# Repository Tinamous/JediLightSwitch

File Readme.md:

Jedi LightSwitch
================

The Jedi Light Switch is a home automation light switch which responds to the Jedi wave or touch(1). It aims to bring the humble wall switch into the modern WiFi lighting era.

1) Automation of modern WiFi lamps (LIFX/Hue) doesn't work if the lamp is switch off at the wall switch.
2) Existing switch may not work as expected for visitors with WiFi bulbs. Often the switch is on but the light off.
3) Switching the lights on/off via an app is annoying.
4) The wall switch may be difficult or impossible to replace with a automation friendly version. (Excludes the Jedi Lightswitch :-) )
5) The existing switch is single use, it switches on or off the main light. In a modern house their are many things this switch can be doing.

The Jedi Light Switch is PCB based with a custom 3D printed enclosure. It is powered by a Particle Photon which uses WiFi and optionally cloud services (i.e. IFTTT.com / Tinamous.com) to control and monitor the room environment.

The Photon may be user programmed so the switch may be heavily customised as desired, even OTA after installation. Likewise lighting control via IFTTT may be modified at will.

As well as acting as a switch it also acts as a room sensor with built-in temperature, humidity and light level measurements which may be used for further automation tasks.

Proximity detection allowing the sensing if somebody is close to the switch. (e.g. Switch the lights on in the room if they are not and somebody is close to the switch as they are probably about to try and switch them on anyway).

Two LEDs controlled by the Photon give the immediate feedback (cloud sevices may take a few seconds to perform the apporpiate operations), these LEDs may also be internet controlled to draw attention to something (i.e. the doorbell ringing).

Why:
----
If you have LIFX or Hue lights they stop working once somebody switches them off at the wall switch which can ruin your automation plans. The Hue has a small switch however the LIFX lights rely on 3rd party products for switching, both suffer from our built-in tendandy to switch the light off at the switch as we leave the room. Neither lights work so well when that happens! Neither Hue or LIFX switch options are immediatly obious that they should be used in preference to the wall switch. Nobody wants to have to train their guests how to switch the lights on or off.

Imaging the scene. You walk into your room, the lights are off but the light switch is on.
* Option 1: Switch the light switch off then on again. This works a charm (but only for the main light).
* Option 2: 
** Find your phone (hopefully it's not somewhere in the dark room you are walking into)
** Unlock your phone
** Launch the LIFX application
** Wait whilst the LIFX applicaiton loads
** Try not to trip or walk into anything as you've continued to walk whilst working your phone in the darkened room
** Scroll to the bulbs or scene you wish to set
** Select the bulbs or scene
** Hopefully the lights respond first time, if not wait a bit and try again
** Put phone away
** Think how great it is you can control your lights from your phone...

Leaving a room:
---------------
Nobody likes to leave the lights on in rooms that are unused or when you go out.....

Imaging you leave the room.
* Option 1: Flick the light switch to switch the light off (goodbye automation).
* Option 2: Find your phone, unlock your phone (you see where this is going).

Neither of these senarios are great. You could replace or remove the light switch...

The Light Switch Problem:
-------------------------
* In the UK we have a different style and voltage requirement for light switchs compared to USA, hence home automation products are slow (if ever) to reach the UK market.
** This is not helped by the need for a CE mark which is slow and expensive.
** Often the switches that are available are extreamly cheap (I've had 5x £30 switches fail when the incandecent bulb blew).
* Most HA light switches require a minimum of 25mm backing box. A lot of UK homes use a 15mm box which either means you need to pad the switch out on the wall (ugly) or replace the box (painful).
* A lot (almost all) HA light switches require "3 wire" configuration. Live, Neutral and switch return. Most UK homes have only 2 wire switches (Live and return).
* Not everybody wants to play with the electrics to get a fancy light switch fitted or pay for an expensive electrician.
** If it's a 2 wire replacement this isn't too difficult, changing the 2 wires to 3 and/or replacing the backing box are a big job.
* If you rent chances are you are not allowed to replace the light switch anyway. Who wants to get thrown out of their rented accomodation for a bit of home automation goodness!
* Switching the lights off at the light switch ruins automation.
* The light switch generally only controlls the main light, occasionally wall lights.
* Switching the wall switch on or off doesn't tell your home automation system that the action has happened so no further actions can happen based on that.
* Theirs no intelligence in the on/off of the humble wall switch. If you walk into a room when you're still half asleep having the light come on at 100% brightness is painful.

The Solution:
-------------
The Jedi Light Switch is designed to remove those problems through a two part solution. The main part is the touch and gesture sensitive WiFi based switch PCB, the second is the enclosure.

The switch and enclosure are designed to be simple to install, no re-wiring required (except for external USB power), a direct replacement for the humble wall switch whilst leaving the switch in place, just hidden behind some sexy technology.

The current enclosure is designed to fit over a UK light switch (sorry rest of the world, It may work in Europe, it certainly won't fit over USA switches). 

The enclosure is 3D printed in two parts:

1) The base. This has an overlap area that fits between the wall and the existing switch to secure the base in place and only requires the switch to be loosened and not removed.
** To fit loosen the screws on the light switch slightly so that the switch comes forward about 2mm.
** Slide the base down the wall so the back fits between the wall and the switch until the top of the switch is as close to the top of the base as it can go.
** Tighten the switch screws, ensuring the enclosure is level. This clamps the base part to the wall. No other fixing is required.
2) The cover:
** This is optional. You may if you wish attach the switch PCB via glue or screws to the base and be done.
** The cover gives a nicer finish to the switch whilst also providing mechanical fixing of the PCB within the base. It may be printed in any colour you can get the 3D filament or resin for, although clear works well.
** Optional: You may also print on a clear "acetate film" to fit between the cover and the PCB with a nice pattern or design over the touch sensor.
** The cover simply slides over the base with the PCB in the middle and stays in place by friction making it easy to remove should you need access to the actual wall switch.

Other Advantages:
* Use of gesture to switch the lights on would work well in dirty/wet areas (e.g. the kitchen) where you may not wish to touch something (e.g. you've half way through cooking chicken).
* The switch supports up, down, near and far waves as well, these may be used to dim the lights, control additional (hall/landing) lighting or something else.
* You don't actually need an existing light switch. The case could be directly attached to the wall or something else to provide easy additional lighting points.
* Other than a USB power pack and WiFi no other external parts are required (no Hub, no dedicated lighting wiring, no ......, not even screws or double sided sticky tape)
* You don't have to be British (but it helps). The switch enclosure and PCB are sized to cover a UK light switch, however as they can be used in stand-alone mode they don't have to be used with a UK switch.
** The SCAD design for the enclosure is provided which may be modified to fit other requirements.
* Intellegent:
** The lights could be dimmed to brightness greadually, especially if the switch knew the room was very dark previously.
** or set to automatically switch off or dim the lifhts after 2 hours.
** or the air-con switched on if the room is hot and humid and the lights have just been switched on (or off).
** the curtains could be closed automatically when the lights are switched on.
** the whole house lights could be switched off if the hall light was switched off (and vica versa, house lights switched on when it's dark when hall/door switch is switched on).

Limitation:
-----------

* Currently requires external USB 5V DC power as the Photon is relativly fairly power hungry device (i.e. using WiFi). Even if a battery was fitted it would require a fair size and to be topped up regularly particularly if the switch is required to respond to network actions (e.g. light LEDs, update firmware etc.).

* Lack of a traditional switch mechanism which may confuse guests. Hopefully the touch ability would be enough to make up for this.

* Cloud services can be slow. Using Photon -> Particle.io -> IFTTT -> LIFX.com -> LIFX bulb can be seconds in the trip which is not idea for a light switch. In this time a new user may have told the switch to switch on/off/on/off/on etc a number of times.

Future upgrades:
----------------

Planned for V1.1:
* 2 LEDs in the bottom corners to match the top so each corner has an LED.
* Back lighting. Adding more LEDs to project backwards to light up the enclosure (works best for clear enclosures). Ideally NeoPixel type so they can be controlled from 1 wire and have a range of colour / intensity controlled.

Future posabilities:
* Split/Dual touch sensor pads so that it works for hall/landing lights (up/down) or duel lighting modes in a room (main/wall lights).
* RS485 interface, supply 5V to Photon from a RS485 with 12V house wired RS485 network, interface with other RS485 HA devices and provide a more reliable connection and power.
** This is easier then putting a PoE Ethernet connection on the switch.
* Battery + charger
* Improved interrupt's that can be used to wake the Photon (currently 2 interupts, one high and one low which can't both be used to wake the Photon) to improve battery life.
* Buzzer
* IR Sender to allow the switch to send out instructions from automation requests (e.g. telly on) or relay the signal from room to room.
* IR Receiver to allow remove control of the switch and/or transmission from room to room.
* Microphone (to decect noise levels rather than listen).
* PIR sensor
* Improved temp/humidity sensor for one of the new Bosch line with BP and gas sensing as well.

License:
--------
Licensed under Creative Commons ShareAlike 4.0 https://creativecommons.org/licenses/by-sa/4.0/

Restrictions: May not be used to control lighting on a death star.

Notes:
------
1) Also responds to non-Jedi waves and touch. Not to be used where control by non-Jedi personel is restricted.

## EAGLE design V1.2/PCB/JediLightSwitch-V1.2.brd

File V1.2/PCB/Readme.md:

Jedi LightSwitch PCB.
=====================

Licensed under Creative Commons ShareAlike 4.0 https://creativecommons.org/licenses/by-sa/4.0/

PCB Fabrication by OSH Park.
PCB: <TODO: Insert PCB link>

PCB Stensil by OSH Stencil (https://oshstencils.com/).

PCB Assembly Notes:
-------------------
APDS-9960 and HTU21D are tricky components to solder onto the board. The switch may be used without them if you wish to not solder them and prefer to use touch only.

Use either a hot air gun for solder reflow or reflow oven for the top layer. Use a stencil from OSH Stencils and place U1/U2 (APDS-9960 and HTU21D) carefully. 

Using a low flow and a temperature appropriate for the solder paste heat the board around U1/U2 bringing until the solder melds. Allow a little longer for U1 as the solder is not visible.

The bottom of the board should be hand solderered to prevent U1/U2 dropping off. Most parts are 1206 or 0805 and not overly difficult. U4 (AT42QT1010) is a little difficult but excess solder can be removed with solder wick if needed.

The value of C4 may need to be adjusted to increase/reduce sensitivity. 10nF was found to be to little. 68nF was overly sensitive.

The value of R5/R6 should be selected based on the required brightness of the LEDs and the LED selected.

Resources:
----------
SparkFun Eagle Library and breakout boards used under CC-SA.

SparkFun Eagle Library: https://github.com/sparkfun/SparkFun-Eagle-Libraries

SparkFun APDS-9960 breakout: https://www.sparkfun.com/products/12787
SparkFun HTU21D breakout: https://www.sparkfun.com/products/12064
SparkFun AT42QT1010 breakout: https://www.sparkfun.com/products/12041

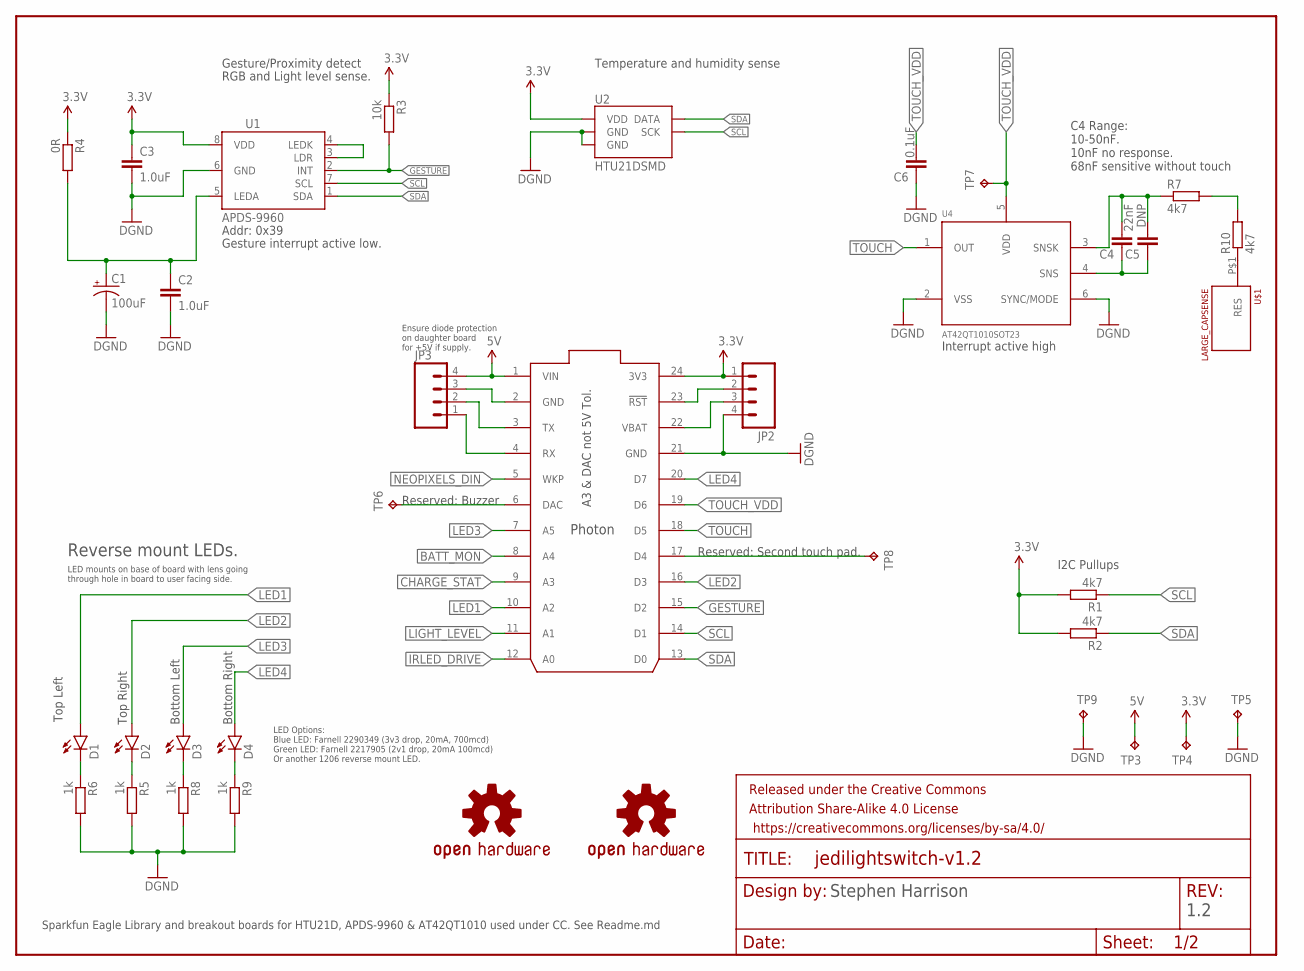
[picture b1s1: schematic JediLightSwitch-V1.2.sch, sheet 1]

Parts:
C1: 100uF; EIA7343
C2, C3: 1.0uF; C0805
C4: 22nF; C0805
C5: DNP; C0805
C6: 0.1uF; C0805
D1, D2, D3, D4: LED1206-BOTTOM; LED-1206-BOTTOM
FRAME2: FRAME-LETTER; CREATIVE_COMMONS
JP2, JP3: M04SMD_STRAIGHT_COMBO; 1X04_SMD_STRAIGHT_COMBO
LOGO1, LOGO2: OSHW-LOGOM; OSHW-LOGO-M
R1, R2, R7, R10: 4k7; R0805
R3: 10k; R0805
R4: 0R; R0805
R5, R6, R8, R9: 1k; R0805
TP3, TP5, TP6, TP7, TP8, TP9: TPTP20R; TP20R
TP4: 3v3; TP20R
U1: APDS-9960
U2: HTU21DSMD; HTU21D
U3: PHOTON_SMD
U4: AT42QT1010SOT23; SOT23-6
U$1: LARGE_CAPSENSE

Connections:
3.3V: C3.1, JP2.1, R1.2, R2.2, R3.1, R4.1, TP4.TP, U1.8 (VDD), U2.VDD, U3.24 (3V3); also elsewhere on the board
5V: JP3.4, TP3.TP, U3.1 (VIN); also elsewhere on the board
BATT_MON: U3.8 (A4); also elsewhere on the board
CHARGE_STAT: U3.9 (A3); also elsewhere on the board
D4: TP8.TP, U3.17 (D4)
DAC: TP6.TP, U3.6 (DAC)
GESTURE: R3.2, U1.2 (INT), U3.15 (D2)
GND: C1.C (-), C2.2, C3.2, C6.1, JP2.4, JP3.3, R5.2, R6.2, R8.2, R9.2, TP5.TP, TP9.TP, U1.6 (GND), U2.7 (GND), U2.GND, U3.2 (GND), U3.21 (GND), U4.2 (VSS), U4.6 (SYNC/MODE); also elsewhere on the board
IRLED_DRIVE: U3.12 (A0); also elsewhere on the board
LED1: D1.A, U3.10 (A2)
LED2: D2.A, U3.16 (D3)
LED3: D3.A, U3.7 (A5)
LED4: D4.A, U3.20 (D7)
LIGHT_LEVEL: U3.11 (A1); also elsewhere on the board
unnamed: U1.3 (LDR), U1.4 (LEDK)
unnamed: C1.A (+), C2.1, R4.2, U1.5 (LEDA)
unnamed: D2.C, R5.1
unnamed: D1.C, R6.1
unnamed: JP2.2, U3.23 (!RST)
unnamed: JP2.3, U3.22 (VBAT)
unnamed: R7.2, R10.2
unnamed: R10.1, U$1.P$1
unnamed: JP3.1, U3.4 (RX)
unnamed: JP3.2, U3.3 (TX)
unnamed: C4.2, C5.2, R7.1, U4.3 (SNSK)
unnamed: C4.1, C5.1, U4.4 (SNS)
unnamed: D3.C, R8.1
unnamed: D4.C, R9.1
NEOPIXELS_DIN: U3.5 (WKP); also elsewhere on the board
SCL: R1.1, U1.7 (SCL), U2.SCK, U3.14 (D1); also elsewhere on the board
SDA: R2.1, U1.1 (SDA), U2.DATA, U3.13 (D0); also elsewhere on the board
TOUCH: U3.18 (D5), U4.1 (OUT)
TOUCH_VDD: C6.2, TP7.TP, U3.19 (D6), U4.5 (VDD)

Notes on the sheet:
I2C Pullups
Addr: 0x39
C4 Range: 10-50nF. 10nF no response. 68nF sensitive without touch
Stephen Harrison
1.2
Sparkfun Eagle Library and breakout boards for HTU21D, APDS-9960 & AT42QT1010 used under CC. See Readme.md
Reverse mount LEDs.
LED mounts on base of board with lens going through hole in board to user facing side.
LED Options: Blue LED: Farnell 2290349 (3v3 drop, 20mA, 700mcd) Green LED: Farnell 2217905 (2v1 drop, 20mA 100mcd) Or another 1206 reverse mount LED.
Gesture interrupt active low.
Interrupt active high
Ensure diode protection on daughter board for +5V if supply.
Gesture/Proximity detect
RGB and Light level sense.
Temperature and humidity sense
Top Left
Top Right
Bottom Left
Bottom Right
A3 & DAC not 5V Tol.
Reserved: Second touch pad.
Reserved: Buzzer

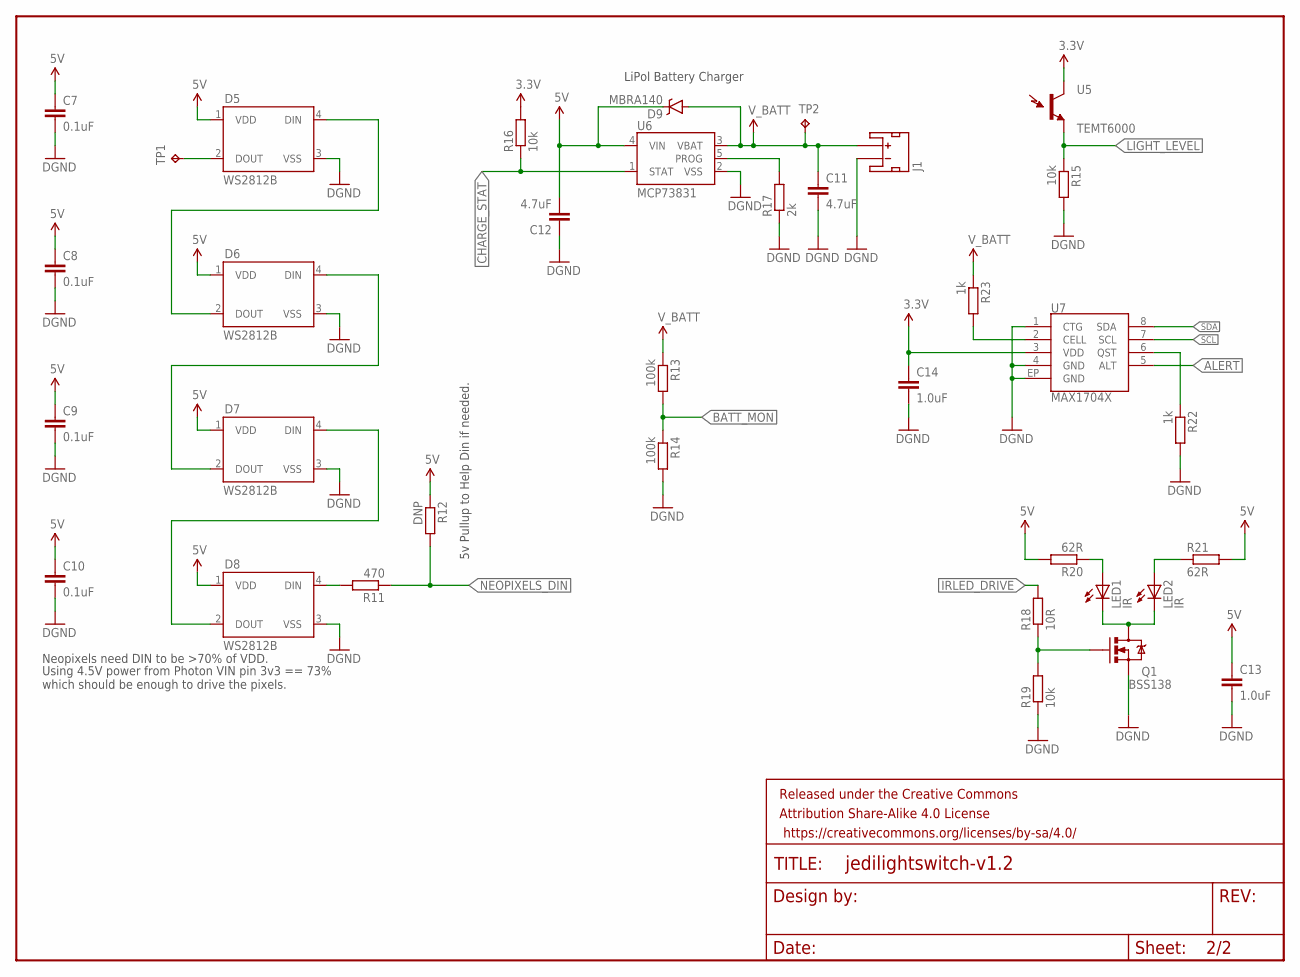
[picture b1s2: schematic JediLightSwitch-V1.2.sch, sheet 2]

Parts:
C7, C8, C9, C10: 0.1uF; C0805
C11, C12: 4.7uF; C0805
C13, C14: 1.0uF; C0805
D5, D6, D7, D8: WS2812B
D9: MBRA140; SMA-DIODE
FRAME1: FRAME-LETTERNO_PACKAGE; DUMMY
J1: JST_2MM_MALE; JST-2-SMD
LED1, LED2: IR; 1206
Q1: BSS138; SOT23-3; FARNELL 9845330
R11: 470; R0805
R12: DNP; R0805
R13, R14: 100k; R0805
R15, R16, R19: 10k; R0805
R17: 2k; R0805
R18: 10R; R0805
R20, R21: 62R; R0805
R22, R23: 1k; R0805
TP1, TP2: TPTP20R; TP20R
U5: TEMT6000; TEMT6000-SEN
U6: MCP73831; SOT23-5
U7: MAX1704X; TDFN-8

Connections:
3.3V: C14.1, R16.2, U5.COLLECTOR (C1), U7.3 (VDD); also elsewhere on the board
5V: C7.1, C8.1, C9.1, C10.1, C12.2, C13.1, D5.1 (VDD), D6.1 (VDD), D7.1 (VDD), D8.1 (VDD), D9.C, R12.1, R20.2, R21.2, U6.4 (VIN); also elsewhere on the board
ALERT: U7.5 (ALT)
BATT_MON: R13.2, R14.1; also elsewhere on the board
CHARGE_STAT: R16.1, U6.1 (STAT); also elsewhere on the board
GND: C7.2, C8.2, C9.2, C10.2, C11.2, C12.1, C13.2, C14.2, D5.3 (VSS), D6.3 (VSS), D7.3 (VSS), D8.3 (VSS), J1.1 (-), Q1.2 (S), R14.2, R15.2, R17.1, R19.1, R22.2, U6.2 (VSS), U7.1 (CTG), U7.4 (GND), U7.EP (GND); also elsewhere on the board
IRLED_DRIVE: R18.2; also elsewhere on the board
LIGHT_LEVEL: R15.1, U5.EMITTER (E1); also elsewhere on the board
unnamed: Q1.1 (G), R18.1, R19.2
unnamed: R17.2, U6.5 (PROG)
unnamed: LED1.A, R20.1
unnamed: D7.4 (DIN), D8.2 (DOUT)
unnamed: R23.2, U7.2 (CELL)
unnamed: D5.2 (DOUT), TP1.TP
unnamed: D6.4 (DIN), D7.2 (DOUT)
unnamed: D5.4 (DIN), D6.2 (DOUT)
unnamed: D8.4 (DIN), R11.2
unnamed: LED2.A, R21.1
unnamed: LED1.C, LED2.C, Q1.3 (D)
unnamed: R22.1, U7.6 (QST)
NEOPIXELS_DIN: R11.1, R12.2; also elsewhere on the board
SCL: U7.7 (SCL); also elsewhere on the board
SDA: U7.8 (SDA); also elsewhere on the board
V_BATT: C11.1, D9.A, J1.2 (+), R13.1, R23.1, TP2.TP, U6.3 (VBAT)

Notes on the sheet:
Neopixels need DIN to be >70% of VDD.
Using 4.5V power from Photon VIN pin 3v3 == 73% which should be enough to drive the pixels.
LiPol Battery Charger
5v Pullup to Help Din if needed.

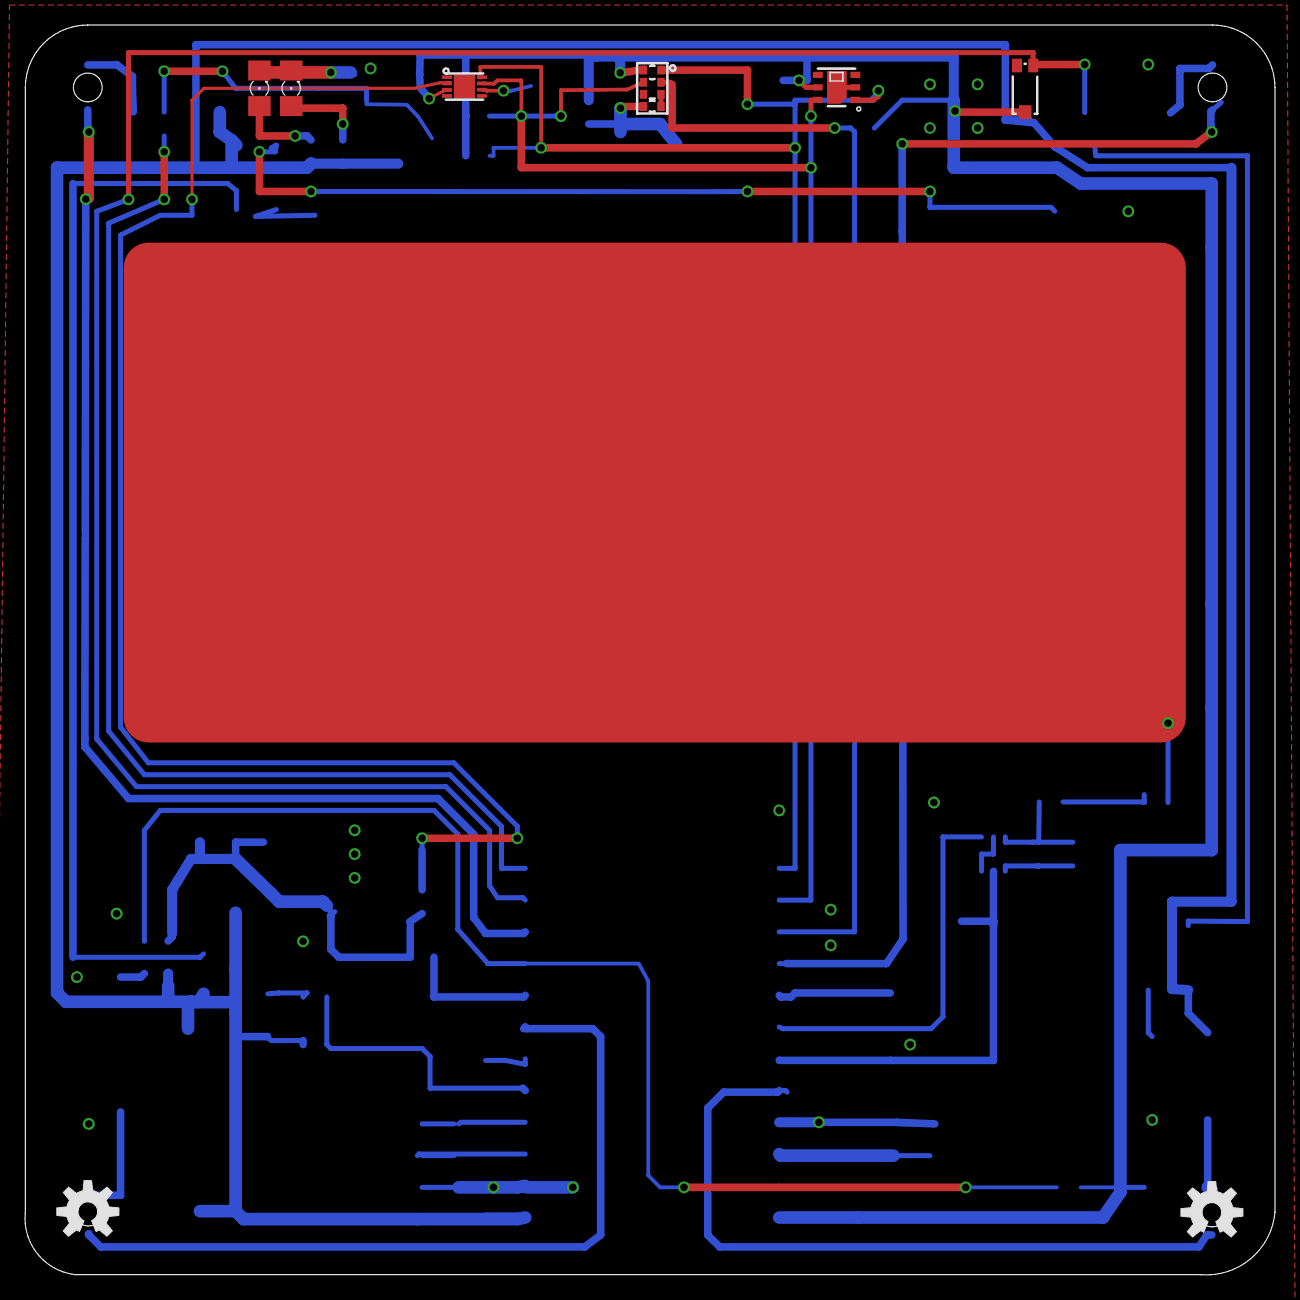
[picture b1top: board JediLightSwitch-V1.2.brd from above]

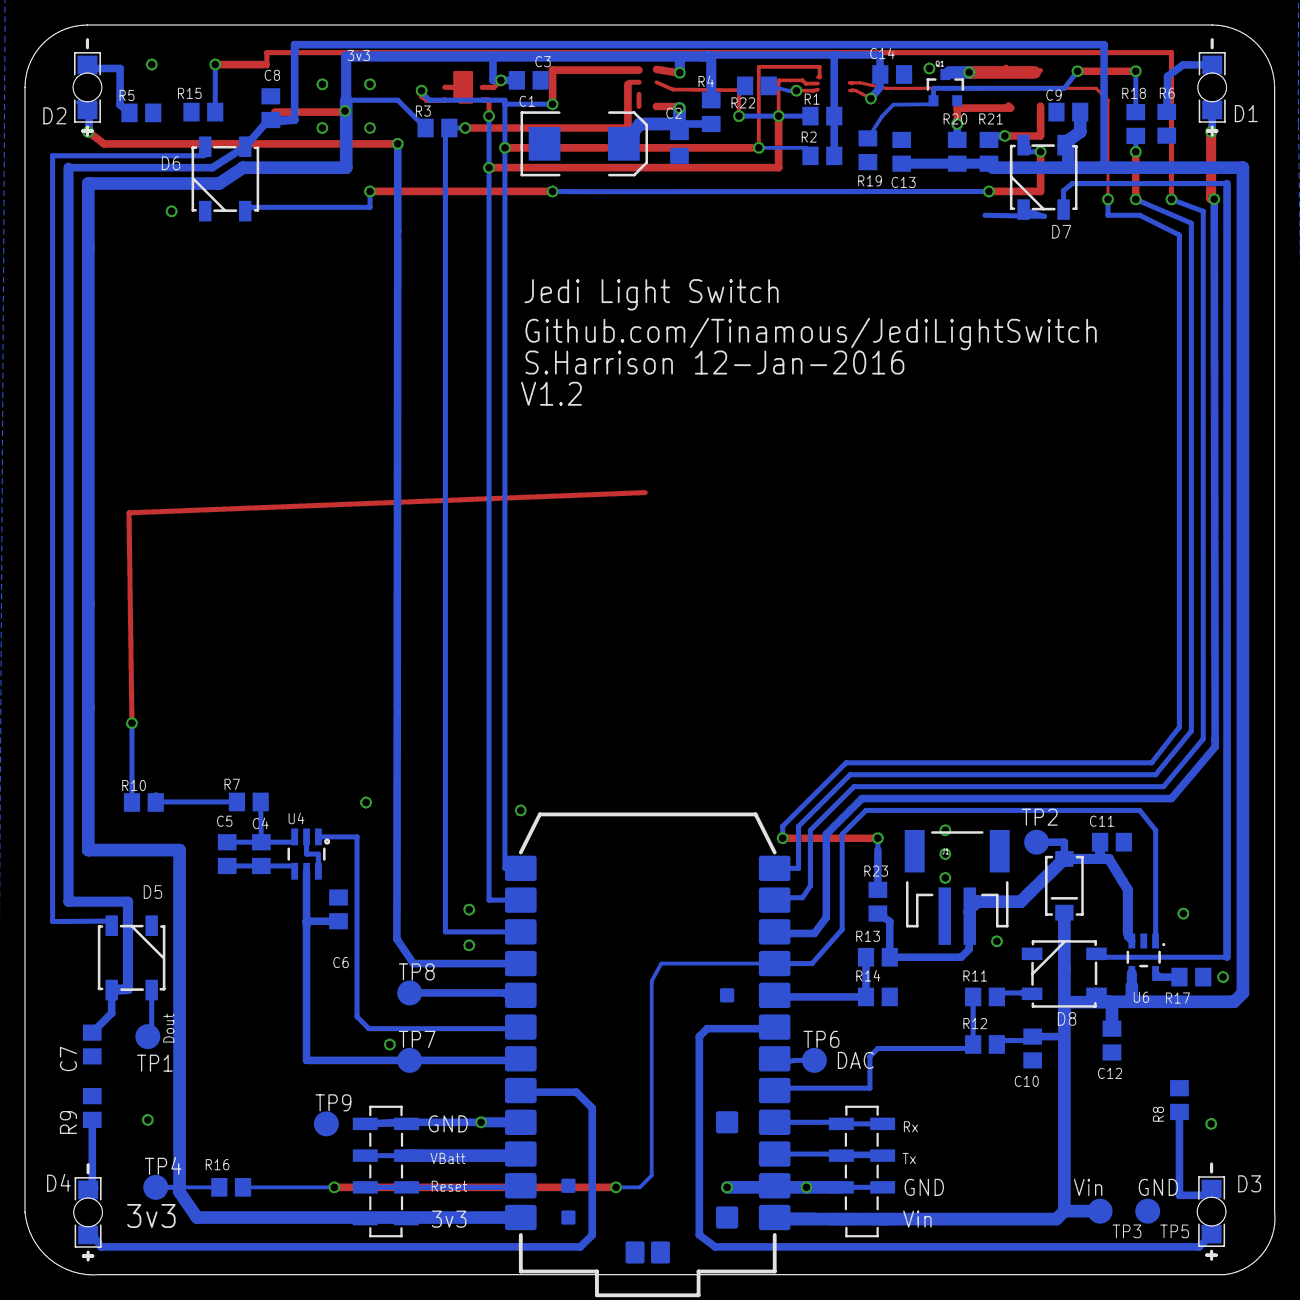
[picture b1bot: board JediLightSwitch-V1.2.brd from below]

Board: 2 copper layers, 100.0 x 100.0 mm, 73 parts (62 on the bottom side), 46 nets.

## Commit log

2016-01-09 Initial working version (V1.0)
2016-01-09 Updated PCB readme.
2016-01-10 Added project readme.
2016-01-10 Modified to give bigger gap between base/cover as the fitting was very tight.
2016-01-10 Updated Schematic & PCB: * Added 2x extra LEDs for bottom left/right. * Added second capacitor and resistor options to cap sense circuit. * Cap sense chip is now powered by Photon to allow for re-cal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
    Bumped revision of cicuit/board to V1.1
2016-01-12 Version 1.2 of Jedi Light Switch as sent to OSH Park.
    Added:
    * 4x back facing NeoPixes.
    * LiPol interface. Charger and monitor.
    * 2x IR LEDs
    * TEMT6000 light sensor as gesture sensor is very direct
    Re-arranged board top so that all the sensors are in a single row.
2016-01-12 Added V1.2 PCB images as generated by OSH Park
2016-02-01 Updated enclosure.
    Removing old stls.
    Added BuildEnclosures.bat to batch build the various sizes of enclosure.
2016-02-01 Added datasheet for APDS9960
2016-02-01 Added start of sample inlays to go between switch cover and PCB.
2016-02-01 Added PCB eagle files.
2016-02-01 Added stl's for base/cover.
2016-02-01 Deleted non-versioned eagle files.
2016-02-01 Removed V1.0 pdf's from this V1.1 branch.
    Updated V1.1 pdf's for the V1.1.1 modification (moved 3v3 rail away from I2C pullups).
2016-02-01 Added gitignore to ignore Eagle temp board/schematic files
2016-02-02 Improved readme.
2016-02-06 Added .gitignore
2016-02-07 Updated resistor values.
2016-02-08 Added minimal option to just give a small frame around the outside.
2016-02-08 Moved V1.1 files into the V1.1 folder & updated gitignore
2016-02-08 Moved PCB files into V1.2/PCB folder to match with V1.1 files, removed enclosure design to prevent clashing with V1.1
2016-02-08 Deleted old pdfs and renamed V1.2 eagle files to include V1.2
2016-02-15 Updated enclosure for 1.2 PCB.
2016-02-15 Added part values
2016-02-15 Split out functionality into version specific classes for improved encapsulation and readability.
    Works for V1.1 and V1.2 boards. Set HARDWARE_REV = 1 or 2 for the appropriate version.

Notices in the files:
parts and their libraries:
SparkFun-Sensors: Licensing: Creative Commons ShareAlike 4.0 International - https://creativecommons.org/licenses/by-sa/4.0
SparkFun-Aesthetics: Released under the Creative Commons Attribution Share-Alike 4.0 License
SparkFun-Aesthetics: Released under the Creative Commons
